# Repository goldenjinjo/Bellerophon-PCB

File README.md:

# hardware
Pronounced: BE-LLER-O-FIN

Pyro-capable Flight Computer with a pressure sensor and IMU. Designed to be general purpose and small enough to fit inside any rocket. Originally developed for UNSW Rocketry Team. 

**PARTS LIST:**

- Microprocessor: Teensy 4
- Barometer/Altimeter: MPL3115A2
- Inertial Measurement Unit (IMU): LSM6DS3
- Memory: XTSD 4GB NAND Flash
- Secondary IMU (optional): Adafruit ICM20948 Breakout Board
- PWM Buzzer
- Individual R, G, B Leds + dedicated programmable LEDs for Barometer, IMU and Flash

---

## 📸 Overview

### 📐 PCB Layout

**Dimensions**: 35.0 mm × 67.6 mm  
**Mounting Holes**: ⌀3.2 mm (4-cornered)

---

### 🔧 Render – Back Side (Component View)

---

### ⚙️ Render – Front Side (Sensor & Output Side)

---

## 📊 Schematic

Includes overcurrent protection, sensor routing, pyro switching, and regulator design for 3.3V and 5V rails.

---

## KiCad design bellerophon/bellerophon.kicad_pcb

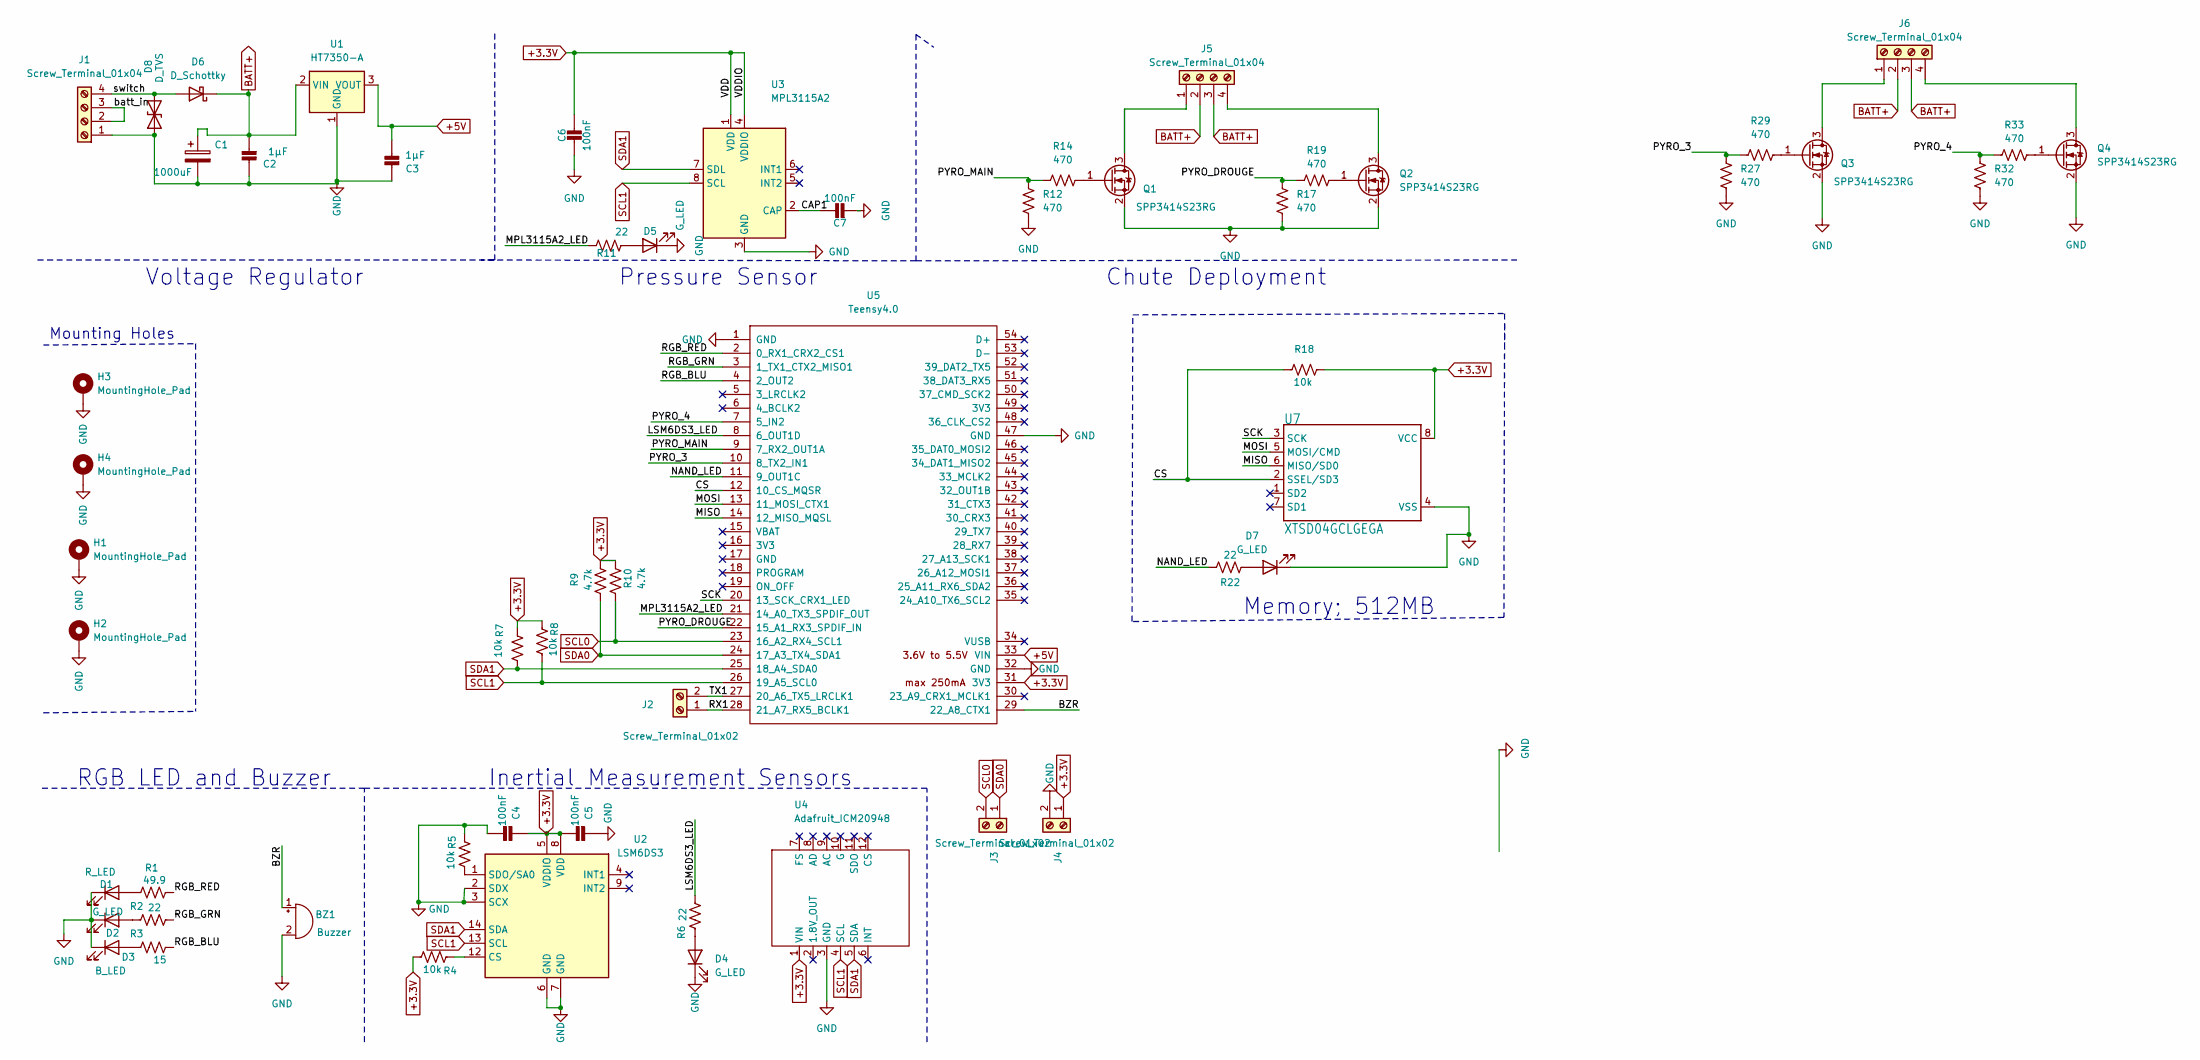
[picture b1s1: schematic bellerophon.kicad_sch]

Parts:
BZ1: Buzzer; YUEXIN YX-SMD5020; LCSC C781883
C1: 1000uF; C_Elec_10x10.2; LCSC C280408
C2, C3: 1µF; C_0805_2012Metric; LCSC C28323
C4, C5, C6, C7: 100nF; C_0603_1608Metric; LCSC C14663
D1: R_LED; LED_0805_2012Metric; LCSC C84256
D2, D4, D5, D7: G_LED; LED_0603_1608Metric; LCSC C72043
D3: B_LED; LED_0603_1608Metric; LCSC C72041
D6: D_Schottky; D_SMA; LCSC Part C22452
D8: D_TVS; D_SOD-323; LCSC Part C127529
H1, H2, H3, H4: MountingHole_Pad; MountingHole_3.2mm_M3_Pad
J1, J5, J6: Screw_Terminal_01x04; SHDR4W100P0X500_1X4_2000X800X1000P
J2, J3, J4: Screw_Terminal_01x02; CONN_282834-2
Q1, Q2, Q3, Q4: SPP3414S23RG; SOT-23; LCSC C114458
R1: 49.9; R_0603_1608Metric; LCSC C23185
R2, R6, R11, R22: 22; R_0603_1608Metric; LCSC C23345
R3: 15; R_0603_1608Metric; LCSC C22810
R4, R5, R7, R8, R18: 10k; R_0603_1608Metric; LCSC C25804
R9, R10: 4.7k; R_0603_1608Metric; LCSC C17673
R12, R14, R19, R27, R29, R32, R33: 470; R_0805_2012Metric; LCSC C17710
R17: 470; R_0805_2012Metric; LCSC C23179
U1: HT7350-A; SOT-89-3; LCSC C7874
U2: LSM6DS3; LGA-14_3x2.5mm_P0.5mm_LayoutBorder3x4y; LCSC C126672
U3: MPL3115A2; NXP_LGA-8_3x5mm_P1.25mm_H1.1mm; LCSC C54429
U4: Adafruit_ICM20948; ICM20946-B25.4x17.78mm-2X06_ROUND-P2.54mm
U5: Teensy4.0; Teensy40
U7: XTSD04GCLGEGA; LGA8_8X6; LCSC C2759953

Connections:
+3.3V: C4.1, C5.2, C6.1, J4.1, R4.2, R7.1, R8.1, R9.2, R10.2, R18.1, U2.5 (VDDIO), U2.8 (VDD), U3.1 (VDD), U3.4 (VDDIO), U4.1 (VIN), U5.31 (3V3), U7.8 (VCC)
+5V: C3.2, U1.3 (VOUT), U5.33 (VIN)
/BZR: BZ1.1 (-), U5.29 (22_A8_CTX1)
/CAP1: C7.1, U3.2 (CAP)
/CS: R18.2, U5.12 (10_CS_MQSR), U7.2 (SSEL/SD3)
/LSM6DS3_LED: R6.2, U5.8 (6_OUT1D)
/MISO: U5.14 (12_MISO_MQSL), U7.6 (MISO/SD0)
/MOSI: U5.13 (11_MOSI_CTX1), U7.5 (MOSI/CMD)
/MPL3115A2_LED: R11.1, U5.21 (14_A0_TX3_SPDIF_OUT)
/NAND_LED: R22.1, U5.11 (9_OUT1C)
/PYRO_3: R27.2, R29.1, U5.10 (8_TX2_IN1)
/PYRO_4: R32.2, R33.1, U5.7 (5_IN2)
/PYRO_DROUGE: R17.2, R19.1, U5.22 (15_A1_RX3_SPDIF_IN)
/PYRO_MAIN: R12.2, R14.1, U5.9 (7_RX2_OUT1A)
/RGB_BLU: R3.2, U5.4 (2_OUT2)
/RGB_GRN: R2.2, U5.3 (1_TX1_CTX2_MISO1)
/RGB_RED: R1.2, U5.2 (0_RX1_CRX2_CS1)
/RX1: J2.1, U5.28 (21_A7_RX5_BCLK1)
/SCK: U5.20 (13_SCK_CRX1_LED), U7.3 (SCK)
/TX1: J2.2, U5.27 (20_A6_TX5_LRCLK1)
/batt_in: J1.2, J1.3
/switch: D6.2 (A), D8.2 (A2), J1.4
BATT+: C1.1, C2.2, D6.1 (K), J5.2, J5.3, J6.2, J6.3, U1.2 (VIN)
GND: BZ1.2 (+), C1.2, C2.1, C3.1, C4.2, C5.1, C6.2, C7.2, D1.1 (K), D2.1 (K), D3.1 (K), D4.1 (K), D5.1 (K), D7.1 (K), D8.1 (A1), H1.1, H2.1, H3.1, H4.1, J1.1, J4.2, Q1.2 (S), Q2.2 (S), Q3.2 (S), Q4.2 (S), R5.1, R12.1, R17.1, R27.1, R32.1, U1.1 (GND), U2.2 (SDX), U2.3 (SCX), U2.6 (GND), U2.7 (GND), U3.3 (GND), U4.3 (GND), U5.1 (GND), U5.32 (GND), U5.47 (GND), U7.4 (VSS)
unnamed: D1.2 (A), R1.1
unnamed: D2.2 (A), R2.1
unnamed: D3.2 (A), R3.1
unnamed: D7.2 (A), R22.2
unnamed: J5.1, Q1.3 (D)
unnamed: J5.4, Q2.3 (D)
unnamed: J6.1, Q3.3 (D)
unnamed: J6.4, Q4.3 (D)
unnamed: Q1.1 (G), R14.2
unnamed: Q2.1 (G), R19.2
unnamed: Q3.1 (G), R29.2
unnamed: Q4.1 (G), R33.2
unnamed: R4.1, U2.12 (CS)
unnamed: R5.2, U2.1 (SDO/SA0)
unnamed: D4.2 (A), R6.1
unnamed: D5.2 (A), R11.2
SCL0: J3.2, R10.1, U5.23 (16_A2_RX4_SCL1)
SCL1: R8.2, U2.13 (SCL), U3.8 (SCL), U4.4 (SCL), U5.26 (19_A5_SCL0)
SDA0: J3.1, R9.1, U5.24 (17_A3_TX4_SDA1)
SDA1: R7.2, U2.14 (SDA), U3.7 (SDL), U4.5 (SDA), U5.25 (18_A4_SDA0)

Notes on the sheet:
Chute Deployment
Memory; 512MB
Mounting Holes
RGB LED and Buzzer
Pressure Sensor
Voltage Regulator
Inertial Measurement Sensors

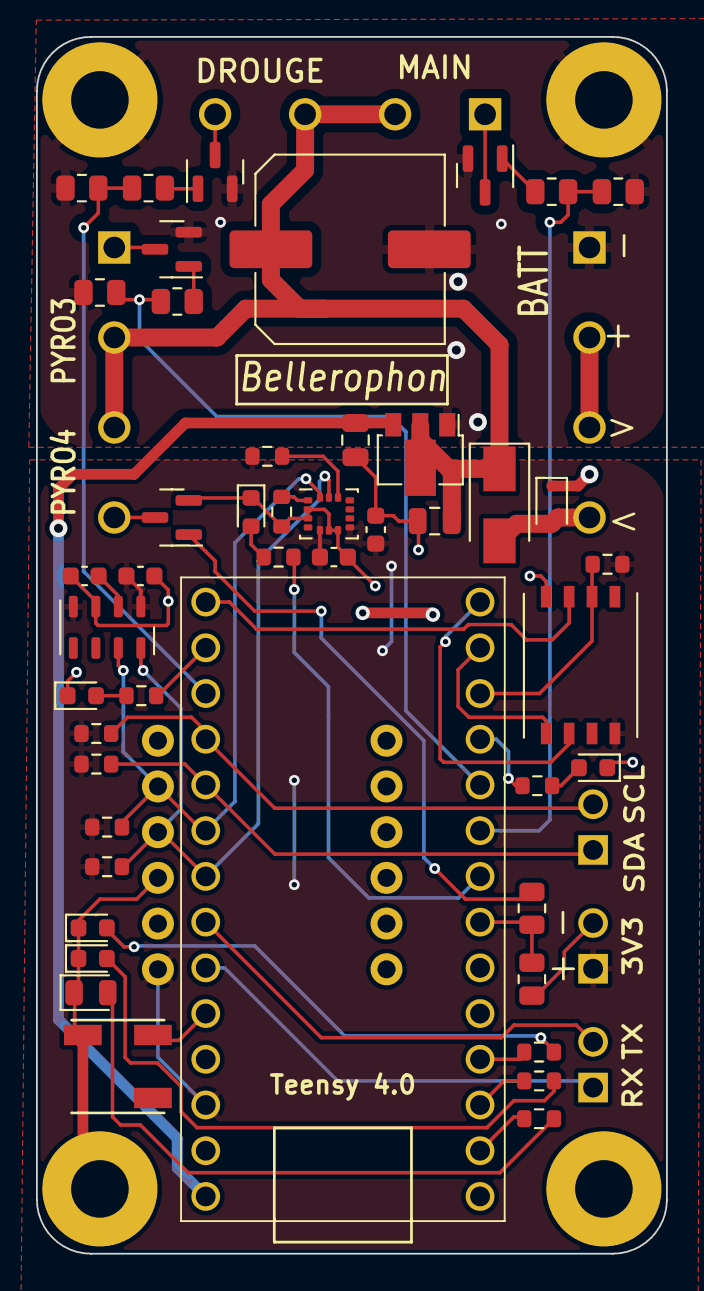
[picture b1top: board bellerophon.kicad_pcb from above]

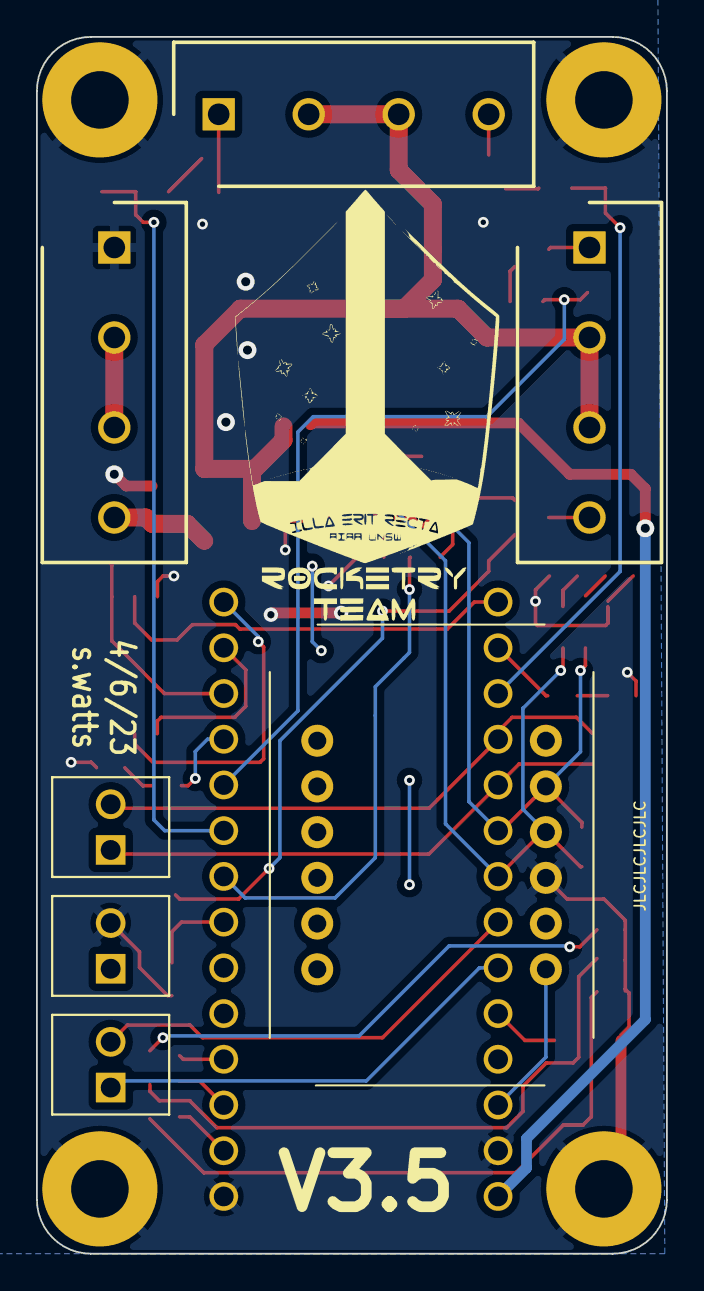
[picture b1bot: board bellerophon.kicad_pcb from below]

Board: 2 copper layers, 35.0 x 67.6 mm, 57 parts (7 on the bottom side), 44 nets.

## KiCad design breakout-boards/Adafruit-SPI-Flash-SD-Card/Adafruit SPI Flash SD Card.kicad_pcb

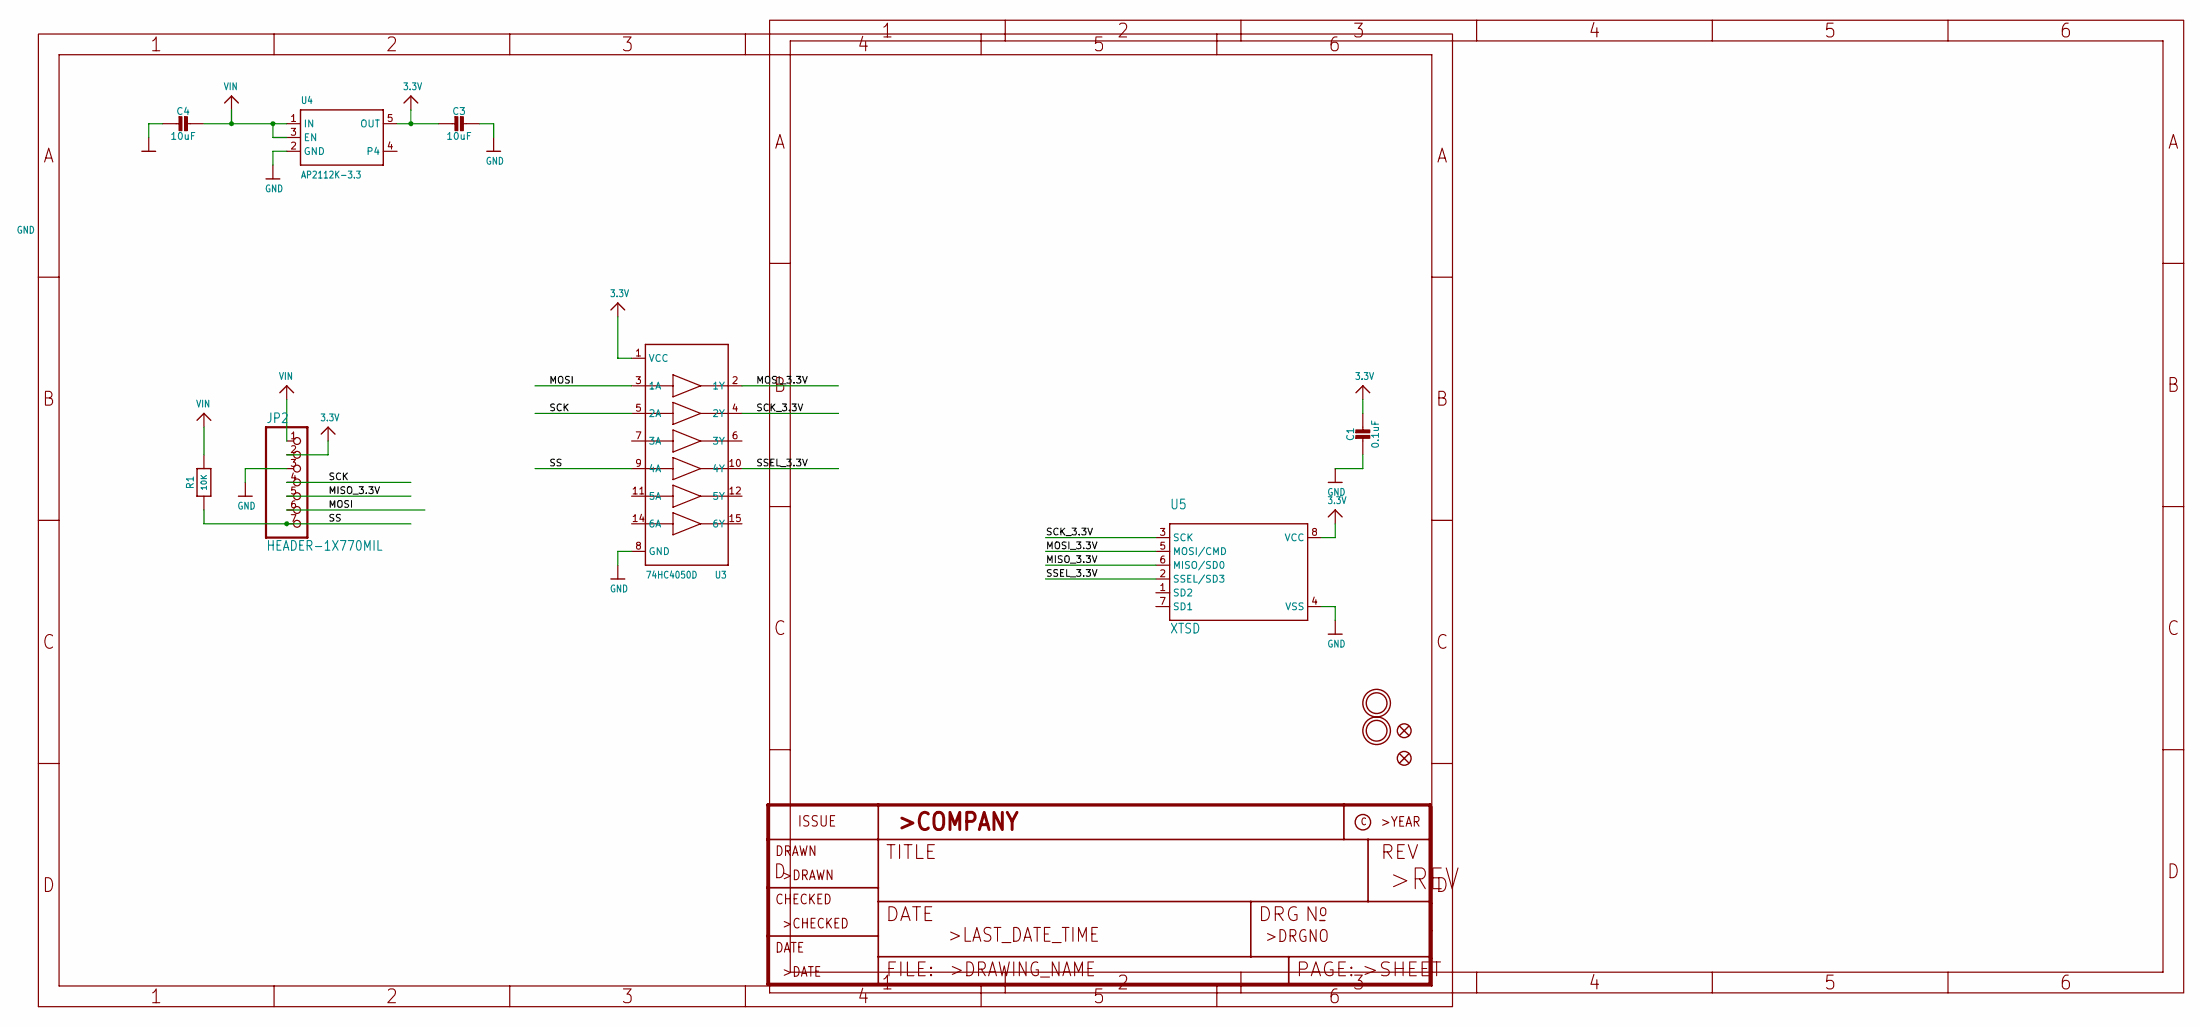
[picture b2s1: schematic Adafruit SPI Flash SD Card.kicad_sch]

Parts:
C1: 0.1uF; 0603-NO
C3, C4: 10uF; 0805-NO
FID2, FID3: FIDUCIAL_1MM
JP2: HEADER-1X770MIL; 1X07_ROUND_70
R1: 10K; 0603-NO
U3: 74HC4050D; TSSOP16
U4: AP2112K-3.3; SOT23-5
U5: XTSD; LGA8_8X6
U$16, U$17: MOUNTINGHOLE2.5; MOUNTINGHOLE_2.5_PLATED

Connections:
3.3V: C1.1, C3.2, JP2.2, U3.1 (VCC), U4.5 (OUT), U5.8 (VCC)
GND: C1.2, C3.1, C4.2, JP2.3, U3.8 (GND), U4.2 (GND), U5.4 (VSS)
MISO_3.3V: JP2.5, U5.6 (MISO/SD0)
MOSI: JP2.6, U3.3 (1A)
MOSI_3.3V: U3.2 (1Y), U5.5 (MOSI/CMD)
SCK: JP2.4, U3.5 (2A)
SCK_3.3V: U3.4 (2Y), U5.3 (SCK)
SS: JP2.7, R1.1, U3.9 (4A)
SSEL_3.3V: U3.10 (4Y), U5.2 (SSEL/SD3)
VIN: C4.1, JP2.1, R1.2, U4.1 (IN), U4.3 (EN)

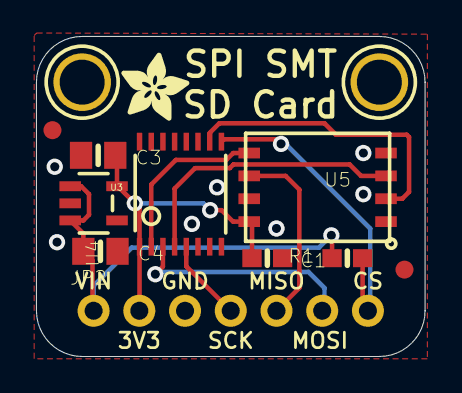
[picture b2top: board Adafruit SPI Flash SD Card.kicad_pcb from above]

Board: 2 copper layers, 21.6 x 17.8 mm, 14 parts (1 on the bottom side), 10 nets.

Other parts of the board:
U$19: ADAFRUIT_3.5MM
U$21: PCBFEAT-REV-040

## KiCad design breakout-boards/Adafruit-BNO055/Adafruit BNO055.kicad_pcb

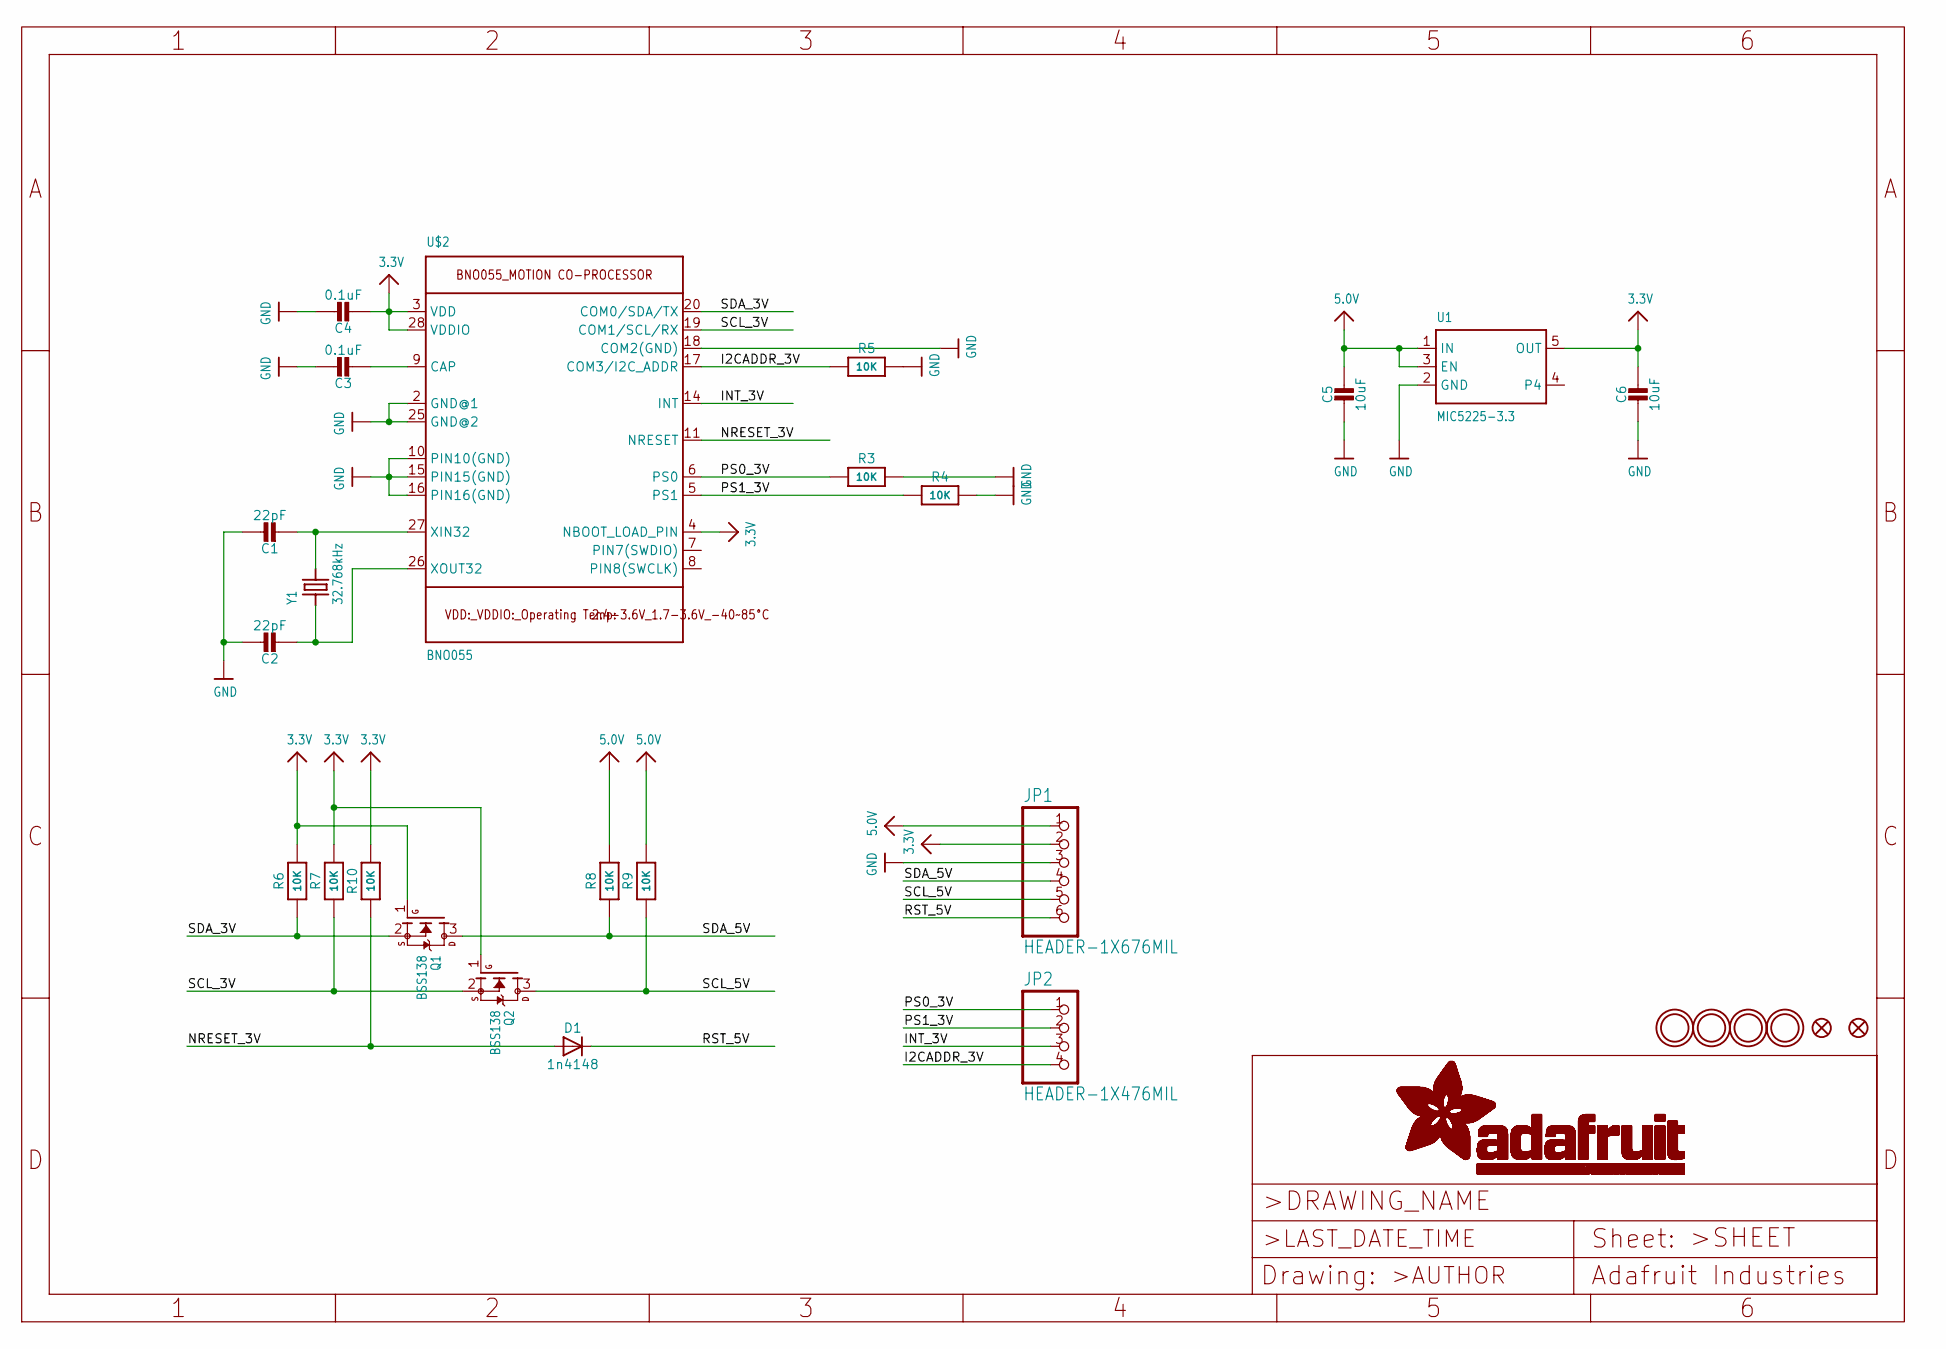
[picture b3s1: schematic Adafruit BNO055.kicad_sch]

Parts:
C1, C2: 22pF; 0805-NO
C3: 0.1uF; 0805-NO
C4: 0.1uF; 0805_10MGAP
C5: 10uF; 0805-NO
C6: 10uF; 0805_10MGAP
D1: 1n4148; SOD-323
FID1, FID2: FIDUCIAL""; FIDUCIAL_1MM
JP1: HEADER-1X676MIL; 1X06_ROUND_76
JP2: HEADER-1X476MIL; 1X04_ROUND_76
Q1, Q2: BSS138; SOT23-WIDE
R3, R4, R5, R6, R7, R10: 10K; 0805-NO
R8, R9: 10K; _0805MP
U1: MIC5225-3.3; SOT23-5
U$2: BNO055
U$29, U$30, U$31, U$32: MOUNTINGHOLE2.5_THICK; MOUNTINGHOLE_2.5_PLATED_THICK
Y1: 32.768kHz; CRYSTAL_8X3.8

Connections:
3.3V: C4.2, C6.1, JP1.2, Q1.1 (G), Q2.1 (G), R6.2, R7.2, R10.2, U1.5 (OUT), U$2.3 (VDD), U$2.4 (NBOOT_LOAD_PIN), U$2.28 (VDDIO)
5.0V: C5.1, JP1.1, R8.2, R9.2, U1.1 (IN), U1.3 (EN)
GND: C1.1, C2.1, C3.1, C4.1, C5.2, C6.2, JP1.3, R3.2, R4.2, R5.2, U1.2 (GND), U$2.2 (GND@1), U$2.10 (PIN10(GND)), U$2.15 (PIN15(GND)), U$2.16 (PIN16(GND)), U$2.18 (COM2(GND)), U$2.25 (GND@2)
I2CADDR_3V: JP2.4, R5.1, U$2.17 (COM3/I2C_ADDR)
INT_3V: JP2.3, U$2.14 (INT)
unnamed: C1.2, U$2.27 (XIN32), Y1.P$4 (2)
unnamed: C2.2, U$2.26 (XOUT32), Y1.P$1 (1)
unnamed: C3.2, U$2.9 (CAP)
NRESET_3V: D1.A, R10.1, U$2.11 (NRESET)
PS0_3V: JP2.1, R3.1, U$2.6 (PS0)
PS1_3V: JP2.2, R4.1, U$2.5 (PS1)
RST_5V: D1.C, JP1.6
SCL_3V: Q2.2 (S), R7.1, U$2.19 (COM1/SCL/RX)
SCL_5V: JP1.5, Q2.3 (D), R9.1
SDA_3V: Q1.2 (S), R6.1, U$2.20 (COM0/SDA/TX)
SDA_5V: JP1.4, Q1.3 (D), R8.1

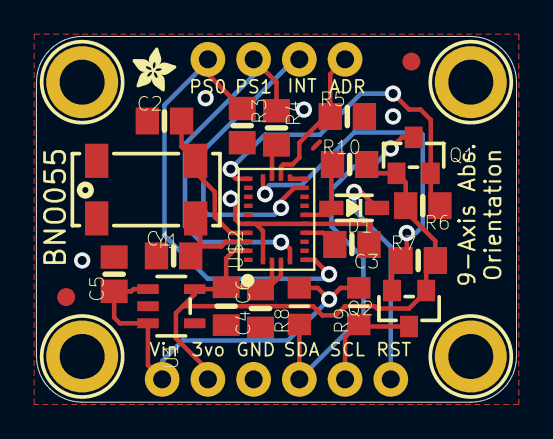
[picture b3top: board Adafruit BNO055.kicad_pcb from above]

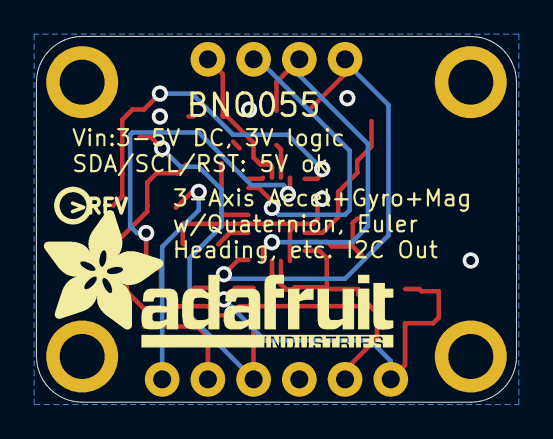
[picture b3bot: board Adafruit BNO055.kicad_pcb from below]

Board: 2 copper layers, 26.7 x 20.3 mm, 31 parts (2 on the bottom side), 16 nets.

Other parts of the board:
U$3: PCBFEAT-REV-040
U$28: ADAFRUIT_TEXT_20MM
U$33: ADAFRUIT_2.5MM

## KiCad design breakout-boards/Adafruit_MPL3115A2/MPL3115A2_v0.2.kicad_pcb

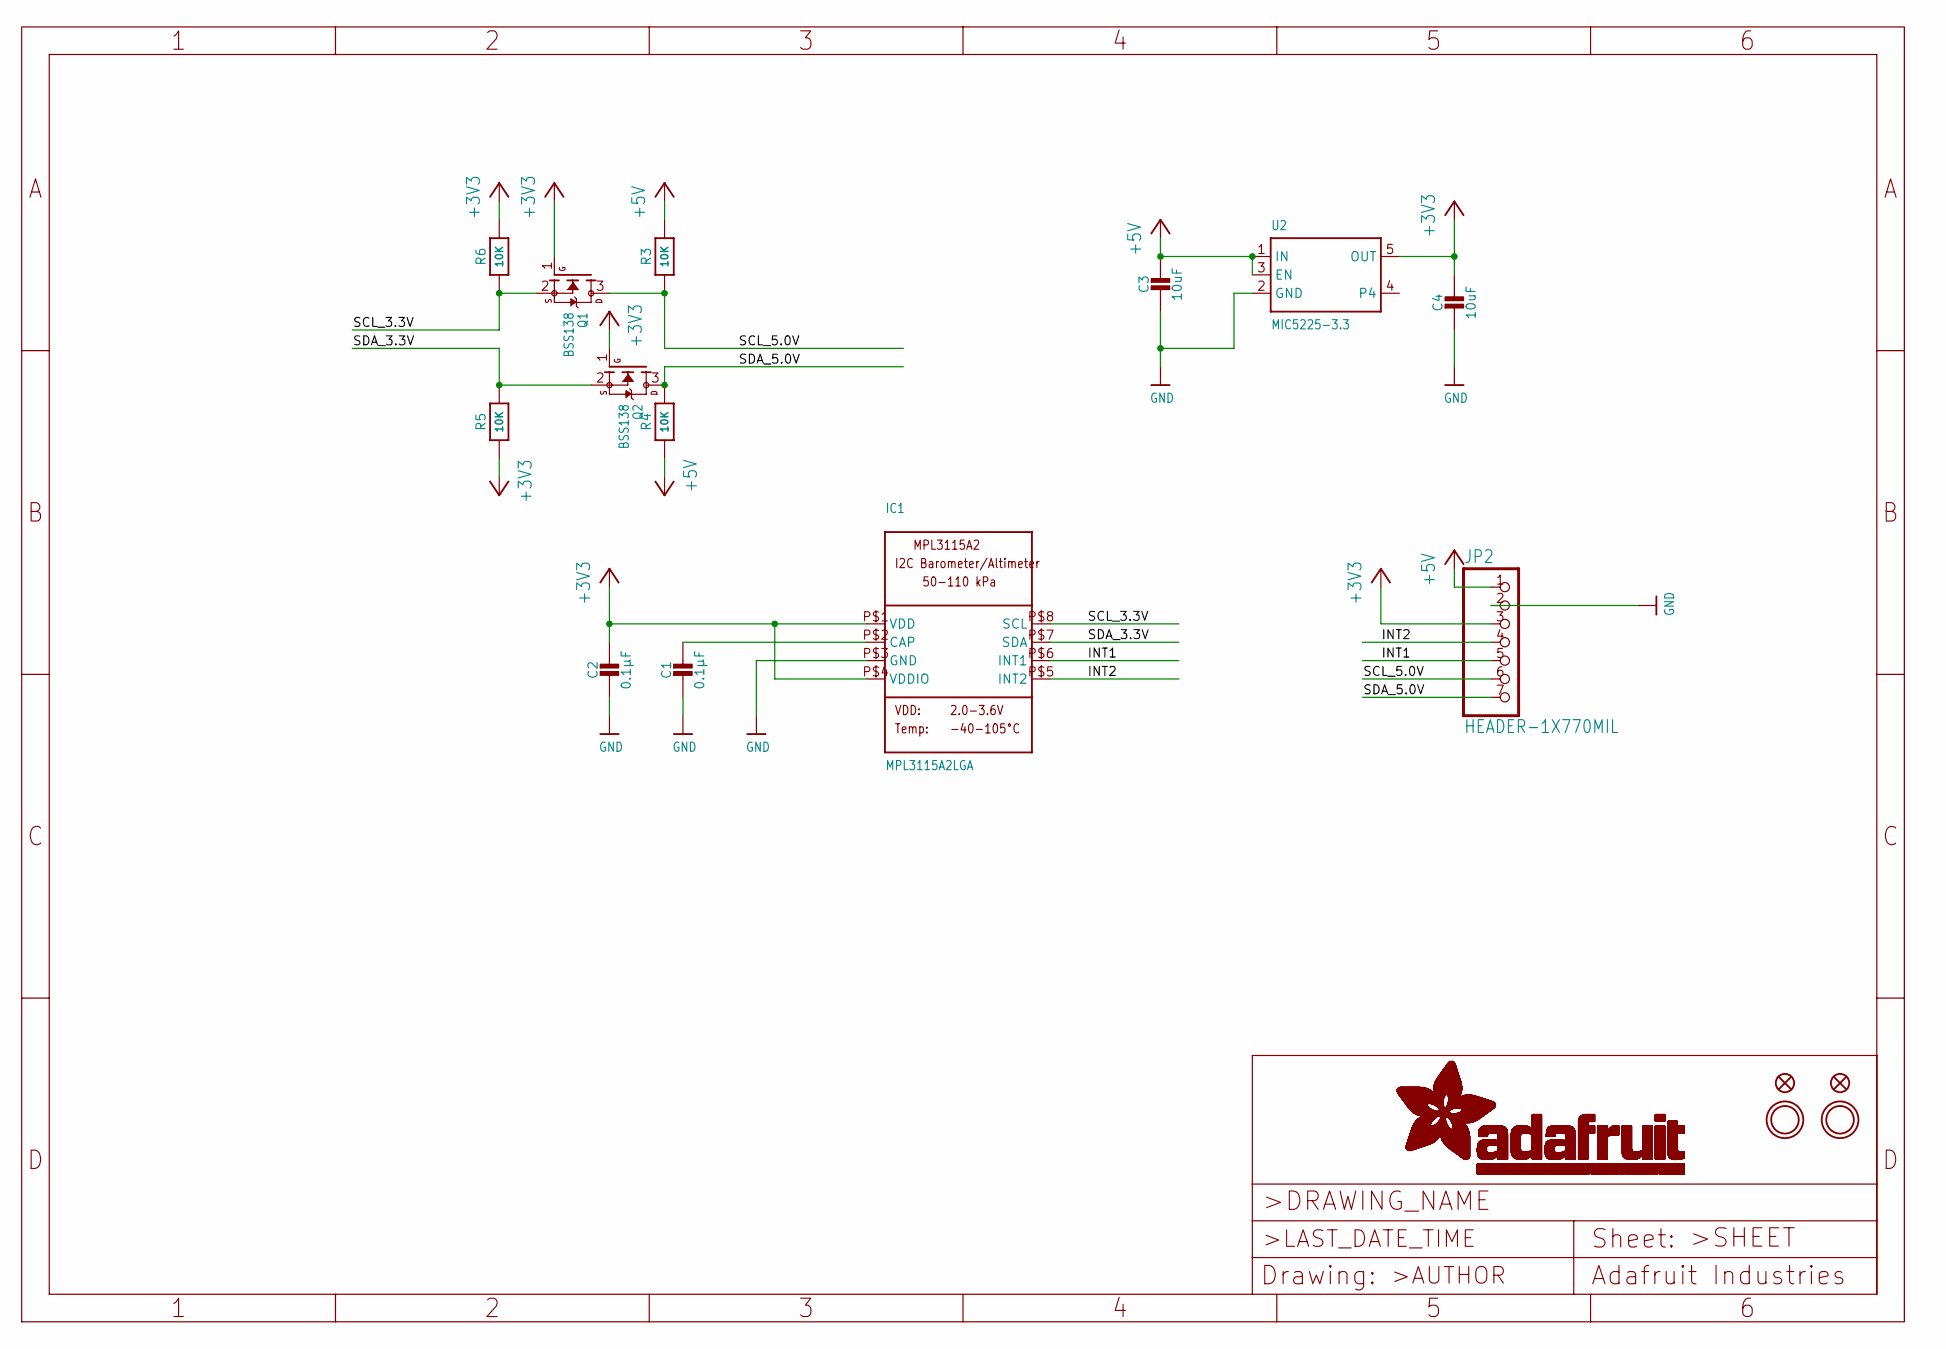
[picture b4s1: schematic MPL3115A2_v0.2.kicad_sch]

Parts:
C1, C2: 0.1µF; 0805-NO
C3, C4: 10uF; 0805-NO
FID1, FID2: FIDUCIAL""; FIDUCIAL_1MM
IC1: MPL3115A2LGA; LGA8
JP2: HEADER-1X770MIL; 1X07_ROUND_70
Q1, Q2: BSS138; SOT23-WIDE
R3, R4, R5, R6: 10K; 0805-NO
U2: MIC5225-3.3; SOT23-5
U$8, U$9: MOUNTINGHOLE2.5; MOUNTINGHOLE_2.5_PLATED

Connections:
+3V3: C2.1, C4.1, IC1.P$1 (VDD), IC1.P$4 (VDDIO), JP2.3, Q1.1 (G), Q2.1 (G), R5.1, R6.2, U2.5 (OUT)
+5V: C3.1, JP2.1, R3.2, R4.1, U2.1 (IN), U2.3 (EN)
CAP: C1.1, IC1.P$2 (CAP)
GND: C1.2, C2.2, C3.2, C4.2, IC1.P$3 (GND), JP2.2, U2.2 (GND)
INT1: IC1.P$6 (INT1), JP2.5
INT2: IC1.P$5 (INT2), JP2.4
SCL_3.3V: IC1.P$8 (SCL), Q1.2 (S), R6.1
SCL_5.0V: JP2.6, Q1.3 (D), R3.1
SDA_3.3V: IC1.P$7 (SDA), Q2.2 (S), R5.2
SDA_5.0V: JP2.7, Q2.3 (D), R4.2

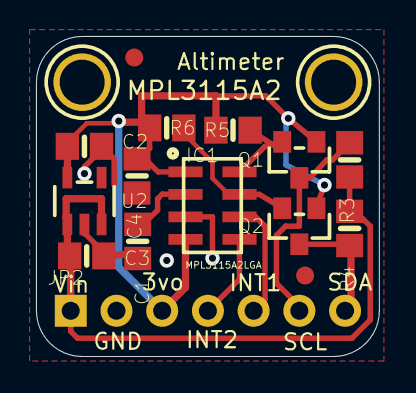
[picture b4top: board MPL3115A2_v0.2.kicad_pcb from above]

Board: 2 copper layers, 19.1 x 17.8 mm, 18 parts (1 on the bottom side), 10 nets.

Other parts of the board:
U$14: ADAFRUIT_3.5MM

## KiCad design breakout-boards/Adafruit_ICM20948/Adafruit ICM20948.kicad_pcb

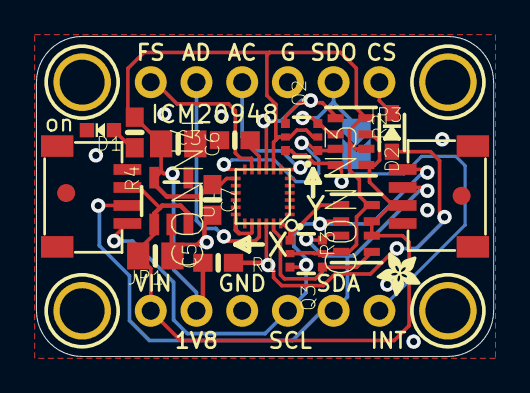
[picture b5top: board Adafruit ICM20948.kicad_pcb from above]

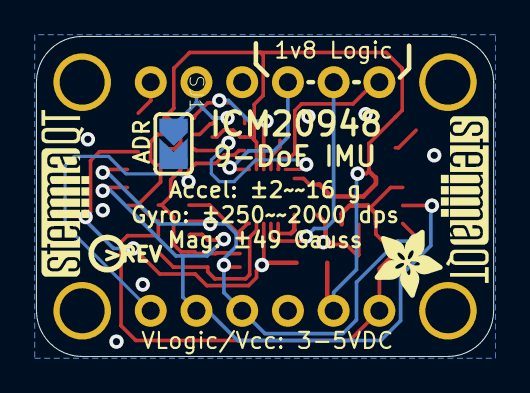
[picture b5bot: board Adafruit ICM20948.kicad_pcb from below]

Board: 2 copper layers, 25.4 x 17.8 mm, 30 parts (5 on the bottom side), 18 nets.

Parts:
C3, C7: 0.1uF; 0603-NO
C5, C6: 10uF; 0805-NO
CONN3, CONN4: STEMMA_I2C_QT; JST_SH4
D1: RED; CHIPLED_0603_NOOUTLINE
D2: 1n4148; SOD-323_MINI
FID2, FID4: FIDUCIAL_1MM
JP1, JP3: 1X06_ROUND_70
Q2, Q3: BSS138; SOT363
R1: 10K; 0603-NO
R2: 4.7K; RESPACK_4X0603
R3: 10K; RESPACK_4X0603
R4: 1K; 0603-NO
SJ1: SOLDERJUMPER_ARROW_NOPASTE
U1: MIC5225-1.8V; SOT23-5
U$2: ADAFRUIT_2.5MM
U$12: ADAFRUIT_3.5MM
U$21: MPU-9250_ICM20948; QFN24_3MM_NOEP
U$38, U$39, U$41, U$42: MOUNTINGHOLE2.5; MOUNTINGHOLE_2.5_PLATED
U$45: PCBFEAT-REV-040
U$46, U$47: STEMMAQT

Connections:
1.8V: C6.1, C7.1, JP1.2, Q2.2, Q2.5, Q3.2, Q3.5, R1.1, R2.6, R2.8, R3.4, R3.8, R4.1, U1.5, U$21.8, U$21.13
AUX_SCL: JP3.4, U$21.7
AUX_SDA: JP3.5, U$21.21
CS: D2.C, JP3.1
CS_1.8V: D2.A, R1.2, U$21.22
FSYNC: JP3.6, U$21.11
GND: C3.2, C5.2, C6.2, C7.2, CONN3.1, CONN3.MT1, CONN3.MT2, CONN4.1, CONN4.MT1, CONN4.MT2, D1.C, JP1.3, JP3.3, SJ1.2, U1.2, U$21.18, U$21.20
INT: JP1.6, Q2.6, R2.4
INT_1.8V: Q2.1, R2.3, U$21.12
unnamed: D1.A, R4.2
REGOUT: C3.1, U$21.10
SCK/SCL: CONN3.4, CONN4.4, JP1.4, Q3.3, R3.6
SCK/SCL_1.8V: Q3.4, R3.1, U$21.23
SDI/SDA: CONN3.3, CONN4.3, JP1.5, Q3.6, R3.7
SDI/SDA_1.8V: Q3.1, R3.5, U$21.24
SDO/ADR: JP3.2, Q2.3, R2.2, SJ1.1
SDO/ADR_1.8V: Q2.4, R2.1, U$21.9
VIN: C5.1, CONN3.2, CONN4.2, JP1.1, R2.5, R2.7, R3.2, R3.3, U1.1, U1.3

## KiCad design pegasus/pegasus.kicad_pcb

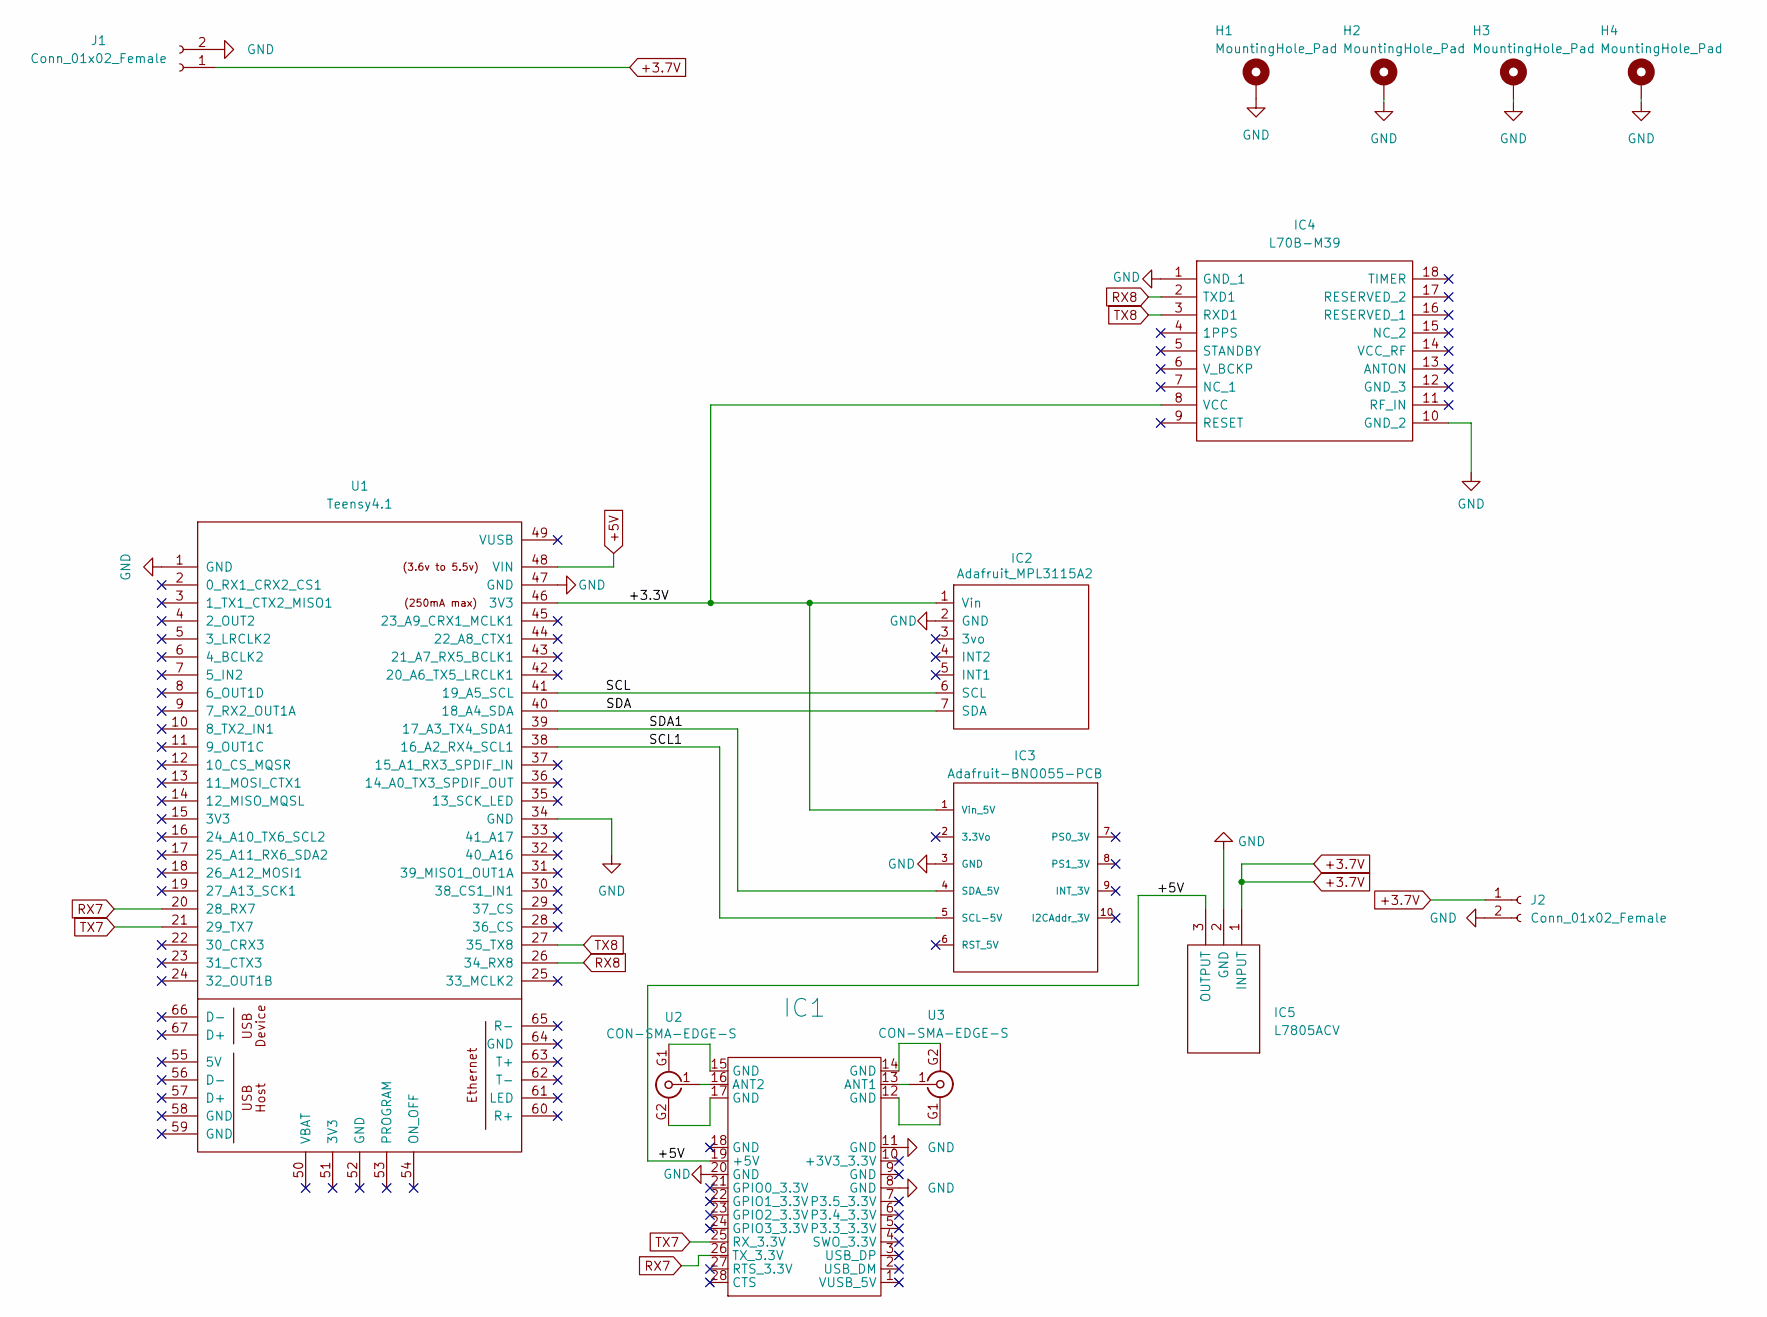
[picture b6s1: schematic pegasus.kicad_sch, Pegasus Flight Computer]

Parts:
H1, H2, H3, H4: MountingHole_Pad; MountingHole_2.2mm_M2_Pad
IC1: 1x28
IC2: Adafruit_MPL3115A2; 1x07
IC3: Adafruit-BNO055-PCB; adafruit_
IC4: L70B-M39; 1x18; Manufacturer_Part_Number L70B-M39; Mouser Part Number 277-L70B-M39
IC5: L7805ACV; TO255P460X1020X2008-3P; Manufacturer_Part_Number L7805ACV
J1, J2: Conn_01x02_Female; PinHeader_1x02_P2.00mm_Vertical
U1: Teensy4.1; Teensy_4.1
U2, U3: CON-SMA-EDGE-S; RFSOLUTIONS_CON-SMA-EDGE-S

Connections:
+3.7V: IC5.1 (INPUT), J1.1, J2.1
+5V: IC1.19 (+5V), IC5.3 (OUTPUT), U1.48 (VIN)
/+3.3V: IC2.1 (Vin), IC3.1 (Vin_5V), IC4.8 (VCC), U1.46 (3V3)
/SCL: IC2.6 (SCL), U1.41 (19_A5_SCL)
/SCL1: IC3.5 (SCL-5V), U1.38 (16_A2_RX4_SCL1)
/SDA: IC2.7 (SDA), U1.40 (18_A4_SDA)
/SDA1: IC3.4 (SDA_5V), U1.39 (17_A3_TX4_SDA1)
GND: H1.1, H2.1, H3.1, H4.1, IC1.8 (GND), IC1.11 (GND), IC1.20 (GND), IC2.2 (GND), IC3.3 (GND), IC4.1 (GND_1), IC4.10 (GND_2), IC5.2 (GND), J1.2, J2.2, U1.1 (GND), U1.34 (GND), U1.47 (GND)
unnamed: IC1.12 (GND), U3.G1
unnamed: IC1.13 (ANT1), U3.1
unnamed: IC1.14 (GND), U3.G2
unnamed: IC1.15 (GND), U2.G1
unnamed: IC1.16 (ANT2), U2.1
unnamed: IC1.17 (GND), U2.G2
RX7: IC1.26 (TX_3.3V), U1.20 (28_RX7)
RX8: IC4.2 (TXD1), U1.26 (34_RX8)
TX7: IC1.25 (RX_3.3V), U1.21 (29_TX7)
TX8: IC4.3 (RXD1), U1.27 (35_TX8)

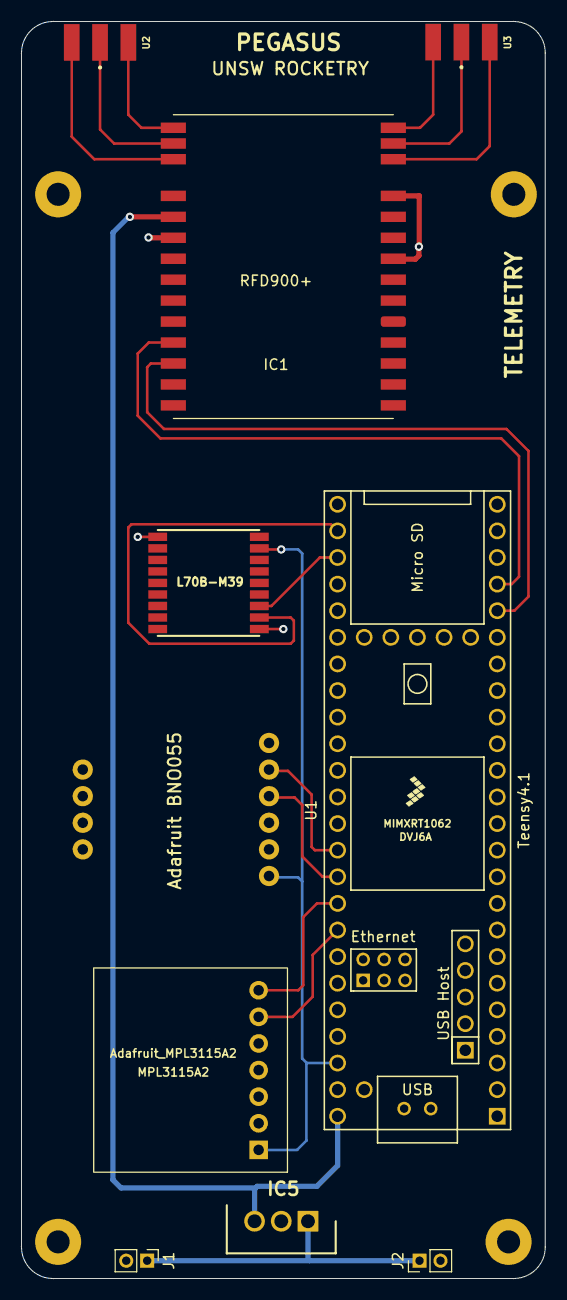
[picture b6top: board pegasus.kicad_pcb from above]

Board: 2 copper layers, 50.0 x 120.0 mm, 14 parts (0 on the bottom side), 18 nets.

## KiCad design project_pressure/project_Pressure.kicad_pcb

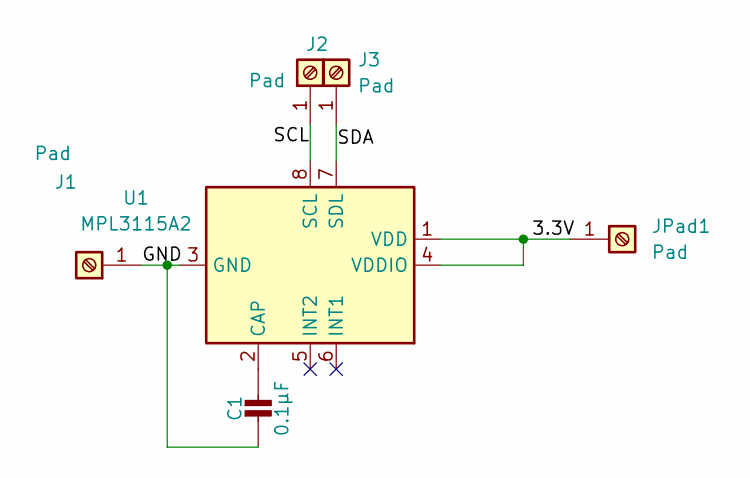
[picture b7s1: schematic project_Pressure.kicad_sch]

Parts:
C1: 0.1µF; C_0504_1310Metric
J1, J2, J3: Pad; TestPoint_Pad_1.5x1.5mm
JPad1: Pad; TestPoint_Pad_1.5x1.5mm
U1: MPL3115A2; NXP_LGA-8_3x5mm_P1.25mm_H1.1mm

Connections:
/3.3V: JPad1.1, U1.1 (VDD), U1.4 (VDDIO)
/GND: C1.2, J1.1, U1.3 (GND)
/SCL: J2.1, U1.8 (SCL)
/SDA: J3.1, U1.7 (SDL)
unnamed: C1.1, U1.2 (CAP)
